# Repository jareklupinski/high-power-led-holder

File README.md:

# high-power-led-holder
Building geometric shapes with slots for high power LEDs

Playing around with ways I can slot in those RGB LED 'stars' in different designs.

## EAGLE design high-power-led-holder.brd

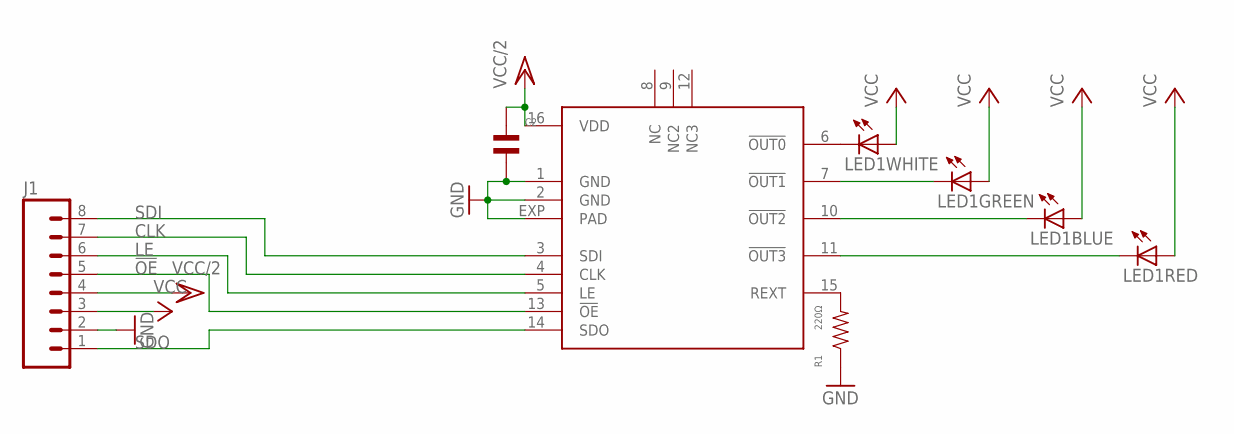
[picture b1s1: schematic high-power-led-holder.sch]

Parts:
C2: CAPACITOR_NP_0805; C0805
IC1: STP04CM05; TSSOP16L
J1: M08; 1X08_ROUND
LED1: 4WLEDBOARD
R1: 220Ω; R0805

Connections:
!OE: IC1.13 (!OE), J1.5
CLK: IC1.4 (CLK), J1.7
GND: C2.P$2, IC1.1 (GND), IC1.2 (GND), IC1.EXP (PAD), J1.2, R1.P$1
LE: IC1.5 (LE), J1.6
unnamed: IC1.7 (!OUT1), LED1.G- (C)
unnamed: IC1.6 (!OUT0), LED1.W- (C)
unnamed: IC1.10 (!OUT2), LED1.B- (C)
unnamed: IC1.11 (!OUT3), LED1.R- (C)
unnamed: IC1.15 (REXT), R1.P$2
SDI: IC1.3 (SDI), J1.8
SDO: IC1.14 (SDO), J1.1
VCC: J1.3, LED1.B+ (A), LED1.G+ (A), LED1.R+ (A), LED1.W+ (A)
VCC/2: C2.P$1, IC1.16 (VDD), J1.4

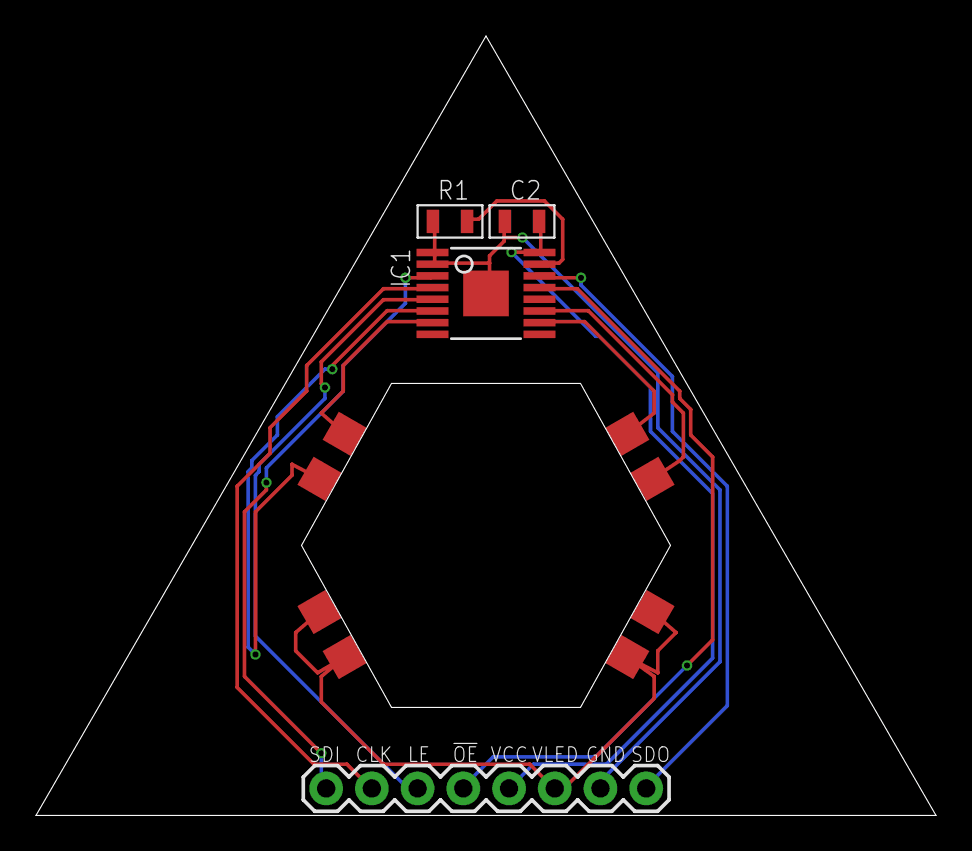
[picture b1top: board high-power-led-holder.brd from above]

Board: 2 copper layers, 50.0 x 43.3 mm, 5 parts (0 on the bottom side), 13 nets.

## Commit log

2018-07-06 design untested

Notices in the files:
parts and their libraries:
SparkFun-Connectors: Licensing: Creative Commons ShareAlike 4.0 International - https://creativecommons.org/licenses/by-sa/4.0
